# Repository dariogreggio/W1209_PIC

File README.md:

# W1209_PIC
a W1209 thermostat clone, made with a PIC, with added USB and OLED

NEW FEATURES: a complete game machine :)

and a fully configurable Timer
1) up to 999 seconds
2) selectable seconds or tenths of seconds (more customizable if needed)
3) start and stop by means of buttons, and external connector
4) stop/reset can be disabled
5) can start automatically at power-on
6) output can be either on or off (reversed mode) during timer operations
7) external input can work as either start or stop
8) complete real-time-clock (date and time) available
9) external output can be used as an analog input to change timing (customized)
12V (5..24V max) operating power supply

and a voltmeter!

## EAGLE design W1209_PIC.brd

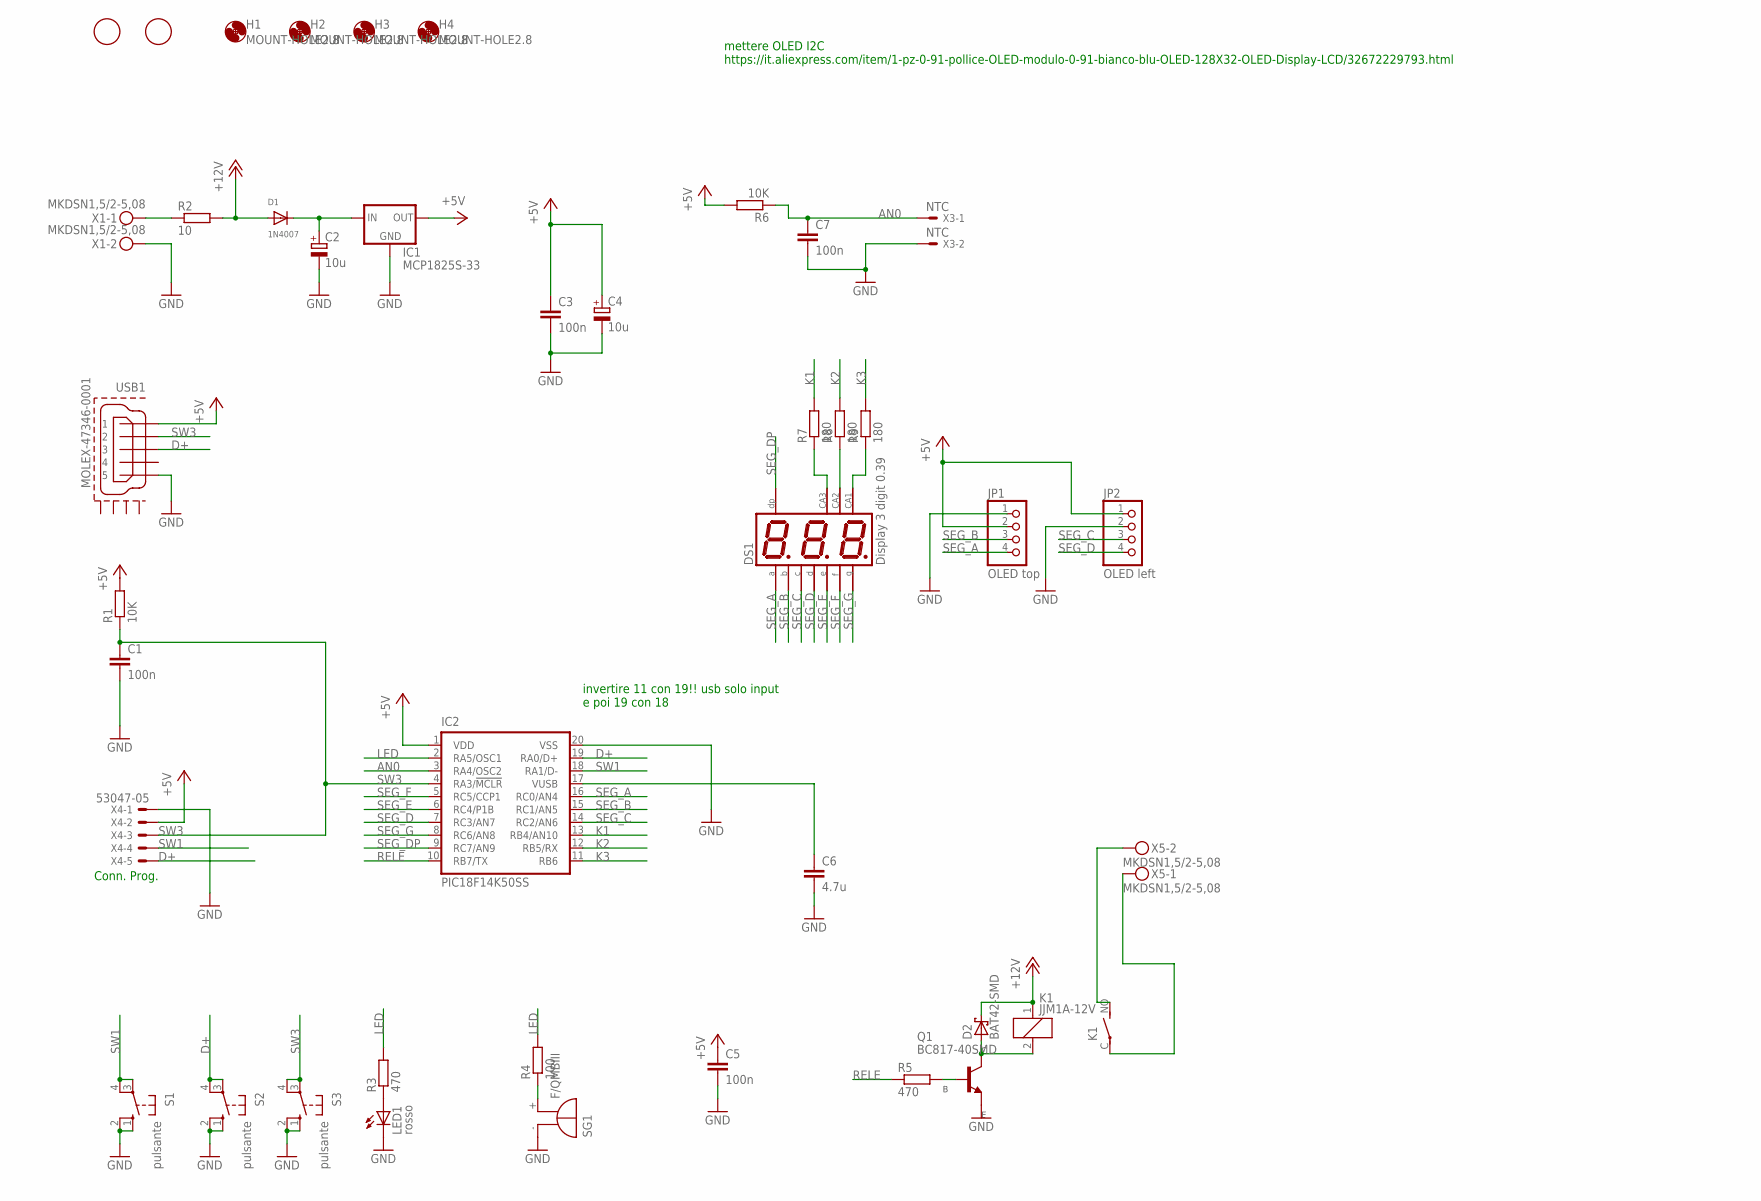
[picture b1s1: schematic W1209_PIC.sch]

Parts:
C1, C3, C5, C7: 100n; C0805
C2: 10u; SMC_C
C4: 10u; SMC_B
C6: 4.7u; C1206
D1: 1N4007; SMADIODE
D2: BAT42-SMD; DO214AC
DS1: Display 3 digit 0.39; KLT36XX
F1, F2: FIDUCIAL; FIDUCIAL_1MM
H1, H2, H3, H4: MOUNT-HOLE2.8; 2,8
IC1: MCP1825S-33; SOT223
IC2: PIC18F14K50SS; SS20
JP1: OLED top; 1X04
JP2: OLED left; 1X04
K1: JJM1A-12V; JJM1A
LED1: rosso; LD260
Q1: BC817-40SMD; SOT23-BEC
R1, R6: 10K; R0805
R2: 10; R2512
R3, R5: 470; R0805
R4: 100; R0805
R7, R8, R9: 180; R0805
S1, S2, S3: pulsante; B3F-10XX
SG1: F/QMBIII
USB1: MOLEX-47346-0001; MOLEX-47364-0001
X1, X5: MKDSN1,5/2-5,08
X3: NTC; KK-156-2
X4: 53047-05

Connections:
+5V: C3.1, C4.+, C5.1, IC1.3 (OUT), IC2.1 (VDD), JP1.2, JP2.1, R1.2, R6.2, USB1.1, X4.2
+12V: D1.A, D2.C, K1.1, R2.2
AN0: C7.1, IC2.3 (RA4/OSC2), R6.1, X3.1
D+: IC2.19 (RA0/D+), S2.3, S2.4 (P1), USB1.3, X4.5
GND: C1.2, C2.-, C3.2, C4.-, C5.2, C6.2, C7.2, IC1.2 (GND), IC1.4 (GND), IC2.20 (VSS), JP1.1, JP2.2, LED1.K (C), Q1.E, S1.1 (S), S1.2 (S1), S2.1 (S), S2.2 (S1), S3.1 (S), S3.2 (S1), SG1.- (+), USB1.5, X1.2, X3.2, X4.1
K1: IC2.13 (RB4/AN10), R7.2
K2: IC2.12 (RB5/RX), R8.2
K3: IC2.11 (RB6), R9.2
LED: IC2.2 (RA5/OSC1), R3.2, R4.2
unnamed: C2.+, D1.C, IC1.1 (IN)
unnamed: D2.A, K1.2, Q1.C
unnamed: K1.C, X5.1
unnamed: K1.NO (S), X5.2
unnamed: R4.1, SG1.+ (-)
unnamed: R2.1, X1.1
unnamed: DS1.P$12 (CA), R7.1
unnamed: DS1.P$8 (CA), R9.1
unnamed: DS1.P$9 (CA), R8.1
unnamed: Q1.B, R5.2
unnamed: LED1.A, R3.1
unnamed: C6.1, IC2.17 (VUSB)
RELE: IC2.10 (RB7/TX), R5.1
SEG_A: DS1.P$11 (A), IC2.16 (RC0/AN4), JP1.4
SEG_B: DS1.P$7 (B), IC2.15 (RC1/AN5), JP1.3
SEG_C: DS1.P$4 (C), IC2.14 (RC2/AN6), JP2.3
SEG_D: DS1.P$2 (D), IC2.7 (RC3/AN7), JP2.4
SEG_DP: DS1.P$3 (DP), IC2.9 (RC7/AN9)
SEG_E: DS1.P$1 (E), IC2.6 (RC4/P1B)
SEG_F: DS1.P$10 (F), IC2.5 (RC5/CCP1)
SEG_G: DS1.P$5 (G), IC2.8 (RC6/AN8)
SW1: IC2.18 (RA1/D-), S1.3, S1.4 (P1), X4.4
SW3: C1.1, IC2.4 (RA3/!MCLR!), R1.1, S3.3, S3.4 (P1), USB1.2, X4.3

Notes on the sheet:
Conn. Prog.
mettere OLED I2C https://it.aliexpress.com/item/1-pz-0-91-pollice-OLED-modulo-0-91-bianco-blu-OLED-128X32-OLED-Display-LCD/32672229793.html
invertire 11 con 19!! usb solo input e poi 19 con 18

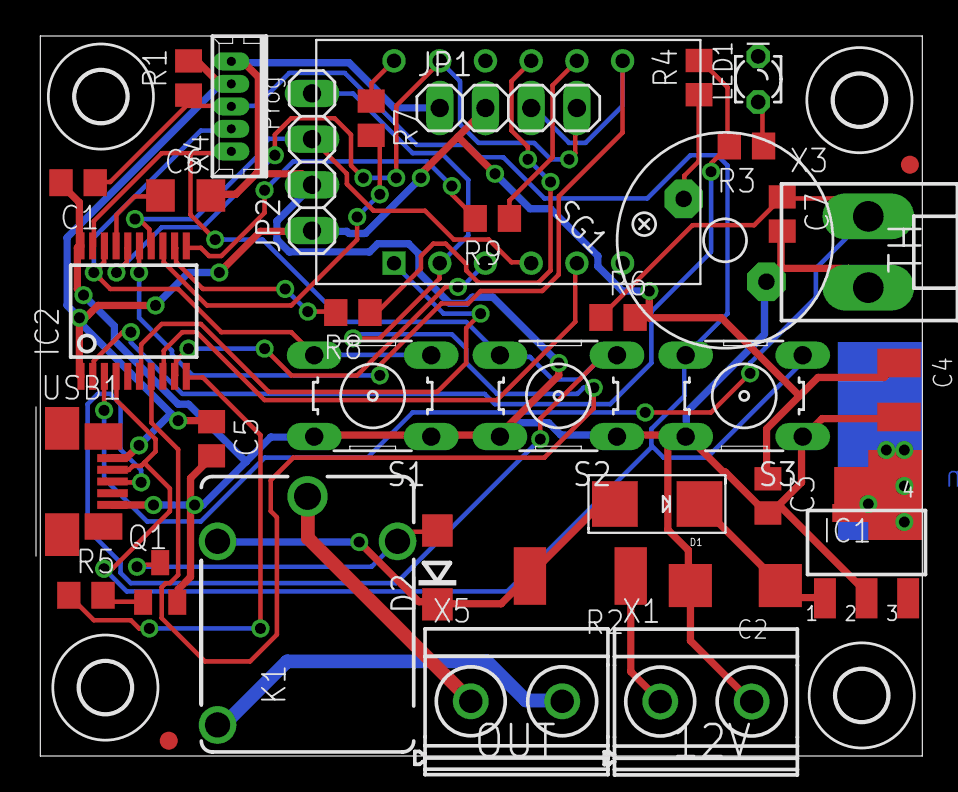
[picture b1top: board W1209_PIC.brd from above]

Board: 2 copper layers, 49.2 x 40.0 mm, 41 parts (0 on the bottom side), 32 nets.

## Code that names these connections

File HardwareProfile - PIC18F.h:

/********************************************************************
 FileName:      HardwareProfile.h
 Dependencies:  See INCLUDES section
 Processor:     PIC18, PIC24, or PIC32 USB Microcontrollers
 Hardware:      The code is natively intended to be used on the 
                  following hardware platforms: 
                    PICDEM FS USB Demo Board
                    PIC18F46J50 FS USB Plug-In Module
                    PIC18F87J50 FS USB Plug-In Module
                    Explorer 16 + PIC24 or PIC32 USB PIMs
                    PIC24F Starter Kit
                    Low Pin Count USB Development Kit
                  The firmware may be modified for use on other USB 
                    platforms by editing this file (HardwareProfile.h)
 Compiler:  	Microchip C18 (for PIC18), C30 (for PIC24), 
                  or C32 (for PIC32)
 Company:       Microchip Technology, Inc.

 Software License Agreement:

 The software supplied herewith by Microchip Technology Incorporated
 (the Company) for its PIC® Microcontroller is intended and
 supplied to you, the Companys customer, for use solely and
 exclusively on Microchip PIC Microcontroller products. The
 software is owned by the Company and/or its supplier, and is
 protected under applicable copyright laws. All rights are reserved.
 Any use in violation of the foregoing restrictions may subject the
 user to criminal sanctions under applicable laws, as well as to
 civil liability for the breach of the terms and conditions of this
 license.

********************************************************************
 File Description:

 Change History:
  Rev   Date         Description
  1.0   11/19/2004   Initial release
  2.1   02/26/2007   Updated for simplicity and to use common coding style
  2.3   09/15/2008   Broke out each hardware platform into its own
                     "HardwareProfile - xxx.h" file
********************************************************************/

#ifndef HARDWARE_PROFILE_PIC18_H
#define HARDWARE_PROFILE_PIC18_H

//#define DEMO_BOARD USER_DEFINED_BOARD

#include "usb_config.h"

//#if defined(USA_USB)			servono cmq se compili la robba usb in progetto...

    //#define USE_SELF_POWER_SENSE_IO
    #define tris_self_power       // Input
    #define self_power          1

    //#define USE_USB_BUS_SENSE_IO
    #define tris_usb_bus_sense      // Input
    #define USB_BUS_SENSE       1 

   
    //Uncomment this to make the output HEX of this project 
    //   to be able to be bootloaded using the HID bootloader
//    #define PROGRAMMABLE_WITH_USB_HID_BOOTLOADER	

    //If the application is going to be used with the HID bootloader
    //  then this will provide a function for the application to 
    //  enter the bootloader from the application (optional)



    /** Board definition ***********************************************/
    //These definitions will tell the main() function which board is
    //  currently selected.  This will allow the application to add
    //  the correct configuration bits as wells use the correct
    //  initialization functions for the board.  These defitions are only
    //  required in the stack provided demos.  They are not required in
    //  final application design.

#if defined(USA_USB) // v. sopra
    #define CLOCK_FREQ 48000000L
    #define GetSystemClock() CLOCK_FREQ   
		#define GetPeripheralClock() (CLOCK_FREQ/4)
#else
    #define CLOCK_FREQ 8000000L
    #define GetSystemClock() CLOCK_FREQ   
		#define GetPeripheralClock() (CLOCK_FREQ/4)
#endif

    /** LED ************************************************************/

		#define mInitAllLEDs()      LATA &= 0b11011111; TRISA &= 0b11011111;
    
		// 
    #define mLED_1              LATAbits.LATA5
    #define mGetLED_1()         mLED_1
    #define mLED_1_On()         mLED_1 = 1;
    #define mLED_1_Off()        mLED_1 = 0;
    #define mLED_1_Toggle()     mLED_1 ^= 1;

    
    /** SWITCH *********************************************************/
    #define mInitSwitch1()      // fisso TRISAbits.TRISA3=1;
    #define mInitSwitch2()      // fisso TRISAbits.TRISA1=1;
    #define mInitSwitch3()      // fisso TRISAbits.TRISA0=1;
    #define mInitAllSwitches()  mInitSwitch1();mInitSwitch2();mInitSwitch3();
#ifndef __DEBUG
    #define sw1                 PORTAbits.RA1
    #define sw2                 PORTAbits.RA0
		#define sw3                 PORTAbits.RA3
#else	// simulatore non va per questi @#£$%
    #define sw1                 SW[0]
    #define sw2                 SW[1]
		#define sw3                 SW[2]
#endif

    #define m_I2CClkBit           LATCbits.LATC0
    #define m_I2CDataBit          LATCbits.LATC1
    #define m_I2CDataBitI         PORTCbits.RC1
    #define m_I2CClkBitI          PORTCbits.RC0
    #define I2CDataTris      TRISCbits.TRISC1
    #define I2CClkTris       TRISCbits.TRISC0
		#define SPI_232_I 			PORTCbits.RC1
		#define SPI_232_IO 			LATCbits.LATC1
		#define SPI_232_I_TRIS 			TRISCbits.TRISC1
		#define SPI_232_O 			LATCbits.LATC0
		#define SPI_232_OI 			PORTCbits.RC0
		#define SPI_232_O_TRIS 			TRISCbits.TRISC0
  
/* 
RC7, pin 9 = seg. DP
RC6, pin 8 = seg. G
RC5, pin 5 = seg. F
RC4, pin 6 = seg. E
RC3, pin 7 = seg. D
RC2, pin 14 = seg. C
RC1, pin 15 = seg. B
RC0, pin 16 = seg. A

RB4, pin = cat 3
RB5, pin = cat 2
RB6, pin = cat 1
*/

    #define m_Rele			          LATBbits.LATB7			// 
    #define m_Ana			          	PORTAbits.RA4			// 

    /** POT ************************************************************/
//    #define mInitPOT()  {AD1PCFGLbits.PCFG5 = 0;    AD1CON2bits.VCFG = 0x0;    AD1CON3bits.ADCS = 0xFF;    AD1CON1bits.SSRC = 0x0;    AD1CON3bits.SAMC = 0b10000;    AD1CON1bits.FORM = 0b00;    AD1CON2bits.SMPI = 0x0;    AD1CON1bits.ADON = 1;}
// 		RB13



    /** I/O pin definitions ********************************************/
    #define INPUT_PIN 1
    #define OUTPUT_PIN 0


#endif  //HARDWARE_PROFILE_H

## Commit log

2023-01-24 Rename W1209_PIC.brd to W1209_PIC.oldbrd
    old version, some pins were unusable
2023-01-24 Rename W1209_PIC.sch to W1209_PIC.oldsch
    some pins were unusable

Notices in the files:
W1209_PIC.brd:
(C) 2023
